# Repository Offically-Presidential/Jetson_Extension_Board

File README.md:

# Jetson_Extension_Board
KiCad design files for the Jetson Extension Board

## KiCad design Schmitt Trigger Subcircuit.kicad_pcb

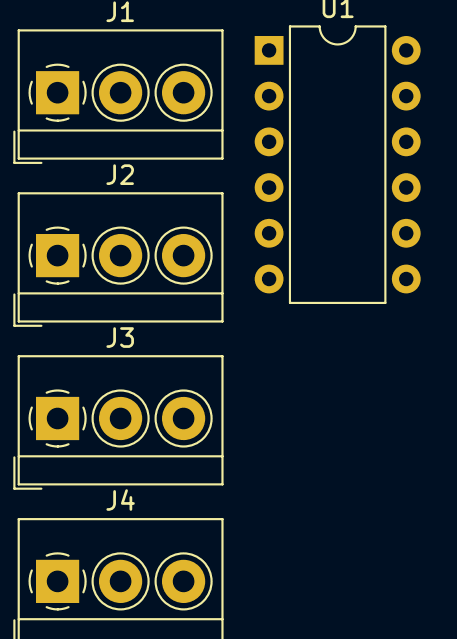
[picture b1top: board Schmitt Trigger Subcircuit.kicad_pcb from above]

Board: 2 copper layers, 5 parts (0 on the bottom side), 6 nets, no tracks yet.

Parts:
J1, J2, J3, J4: Screw_Terminal_01x03; TerminalBlock_4Ucon_1x03_P3.50mm_Horizontal
U1: 74LV14; DIP-12_W7.62mm

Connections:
GND: J1.1, J2.1, J3.1, J4.1, U1.7 (GND)
unnamed: J1.2, U1.1
unnamed: J2.2, U1.3
unnamed: J3.2, U1.5
unnamed: J4.2, U1.9
VCC: J1.3, J2.3, J3.3, J4.3

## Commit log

2024-10-04 Schmitt Trigger Files
2024-10-04 Schmitt Triger Files
2024-10-04 Add Ads1115 subcircuit schematic
2024-10-04 Revert "Add Ads1115 subcircuit schematic"
2024-10-04 adding to Kicad project repo 💀⚡
2024-10-04 all files
2024-10-04 40-Pin Jetson
2024-10-06 Revert "adding to Kicad project repo 💀⚡"
    This reverts commit 5f3dc64a4de30d771f9ba609bccccaec7c3f0d0d.
2024-10-06 IMU-subcircuit-first
2024-10-06 IMU Subcircuit (revised1)
2024-10-06 IMU Subcircuit (revised 2)
2024-10-06 With Footprints done now
2024-10-06 Whole Circuit
2024-10-08 Commiting
